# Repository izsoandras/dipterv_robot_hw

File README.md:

# dipterv_robot_hw
The electrical circuit design of my diploma project.

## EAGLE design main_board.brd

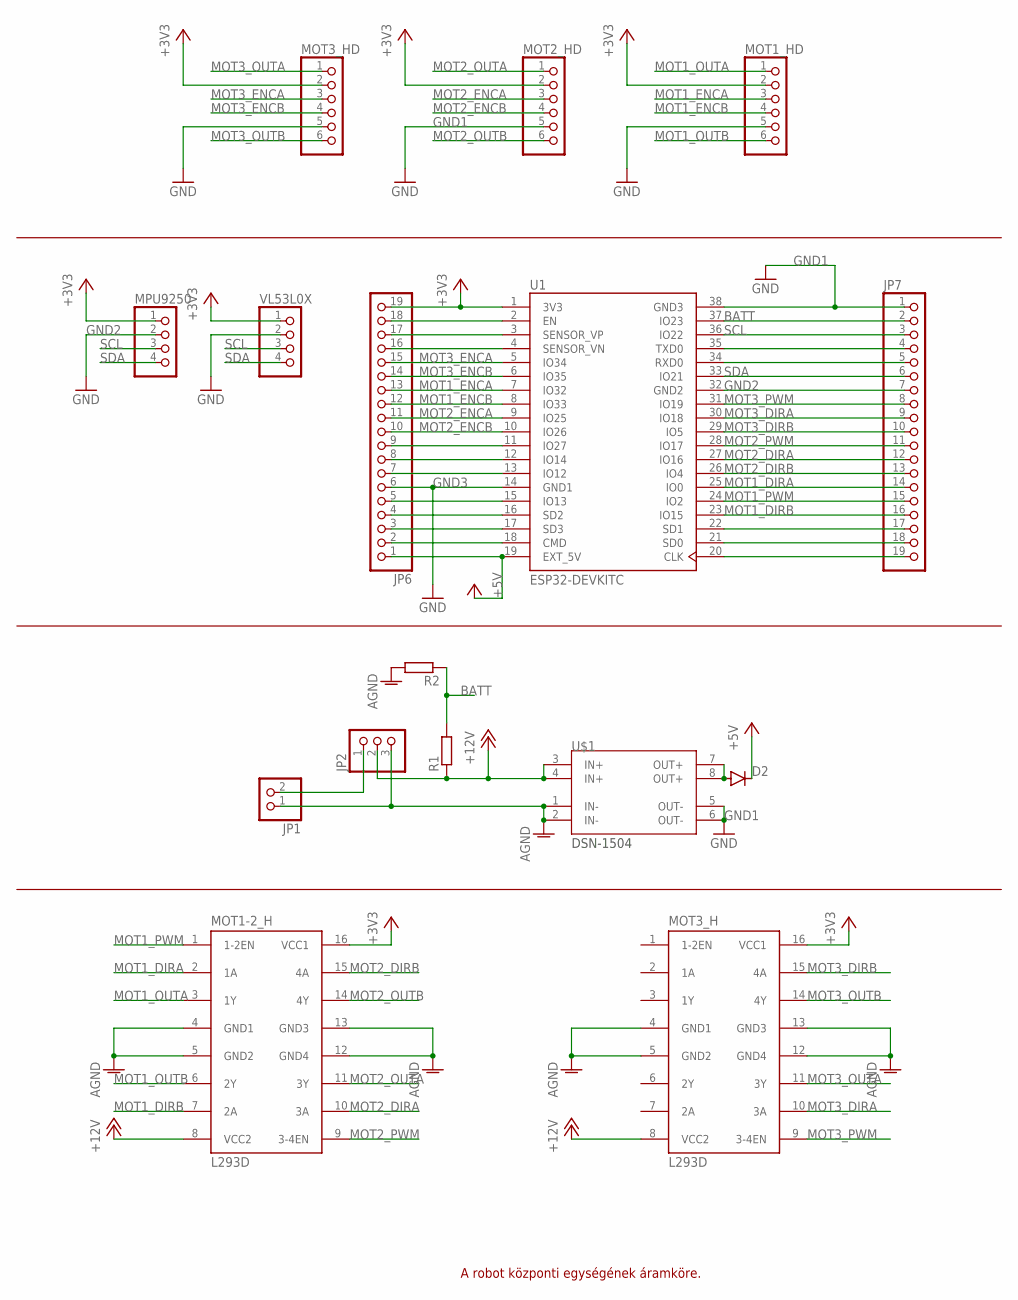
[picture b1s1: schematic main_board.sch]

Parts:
D2: DIODE-DO27-15; DO27-15
JP1: PINHD-1X2; 1X02
JP2: PINHD-1X3; 1X03
JP6, JP7: PINHD-1X19; 1X19
MOT1-2_H, MOT3_H: L293D; DIL16
MOT1_HD, MOT2_HD, MOT3_HD: PINHD-1X6; 1X06
MPU9250: PINHD-1X4; 1X04
R1, R2: R-EU_R0805; R0805
U1: ESP32-DEVKITC; MODULE_ESP32-DEVKITC
U$1: DSN-1504
VL53L0X: PINHD-1X4; 1X04

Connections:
+3V3: JP6.19, MOT1-2_H.16 (VCC1), MOT1_HD.2, MOT2_HD.2, MOT3_H.16 (VCC1), MOT3_HD.2, MPU9250.1, U1.1 (3V3), VL53L0X.1
+5V: D2.C, JP6.1, U1.19 (EXT_5V)
+12V: JP2.2, MOT1-2_H.8 (VCC2), MOT3_H.8 (VCC2), R1.1, U$1.3 (IN+), U$1.4 (IN+)
AGND: JP1.1, JP2.3, MOT1-2_H.4 (GND1), MOT1-2_H.5 (GND2), MOT1-2_H.12 (GND4), MOT1-2_H.13 (GND3), MOT3_H.4 (GND1), MOT3_H.5 (GND2), MOT3_H.12 (GND4), MOT3_H.13 (GND3), R2.2, U$1.1 (IN-), U$1.2 (IN-)
BATT: JP7.2, R1.2, R2.1, U1.37 (IO23)
GND1: JP7.1, MOT2_HD.5, U1.38 (GND3), U$1.5 (OUT-), U$1.6 (OUT-)
GND2: JP7.7, MPU9250.2, U1.32 (GND2)
GND3: JP6.6, MOT1_HD.5, MOT3_HD.5, U1.14 (GND1), VL53L0X.2
MOT1_DIRA: JP7.14, MOT1-2_H.2 (1A), U1.25 (IO0)
MOT1_DIRB: JP7.16, MOT1-2_H.7 (2A), U1.23 (IO15)
MOT1_ENCA: JP6.13, MOT1_HD.3, U1.7 (IO32)
MOT1_ENCB: JP6.12, MOT1_HD.4, U1.8 (IO33)
MOT1_OUTA: MOT1-2_H.3 (1Y), MOT1_HD.1
MOT1_OUTB: MOT1-2_H.6 (2Y), MOT1_HD.6
MOT1_PWM: JP7.15, MOT1-2_H.1 (1-2EN), U1.24 (IO2)
MOT2_DIRA: JP7.12, MOT1-2_H.10 (3A), U1.27 (IO16)
MOT2_DIRB: JP7.13, MOT1-2_H.15 (4A), U1.26 (IO4)
MOT2_ENCA: JP6.11, MOT2_HD.3, U1.9 (IO25)
MOT2_ENCB: JP6.10, MOT2_HD.4, U1.10 (IO26)
MOT2_OUTA: MOT1-2_H.11 (3Y), MOT2_HD.1
MOT2_OUTB: MOT1-2_H.14 (4Y), MOT2_HD.6
MOT2_PWM: JP7.11, MOT1-2_H.9 (3-4EN), U1.28 (IO17)
MOT3_DIRA: JP7.9, MOT3_H.10 (3A), U1.30 (IO18)
MOT3_DIRB: JP7.10, MOT3_H.15 (4A), U1.29 (IO5)
MOT3_ENCA: JP6.15, MOT3_HD.3, U1.5 (IO34)
MOT3_ENCB: JP6.14, MOT3_HD.4, U1.6 (IO35)
MOT3_OUTA: MOT3_H.11 (3Y), MOT3_HD.1
MOT3_OUTB: MOT3_H.14 (4Y), MOT3_HD.6
MOT3_PWM: JP7.8, MOT3_H.9 (3-4EN), U1.31 (IO19)
unnamed: JP6.2, U1.18 (CMD)
unnamed: JP6.3, U1.17 (SD3)
unnamed: JP6.4, U1.16 (SD2)
unnamed: JP1.2, JP2.1
unnamed: D2.A, U$1.7 (OUT+), U$1.8 (OUT+)
unnamed: JP6.8, U1.12 (IO14)
unnamed: JP6.5, U1.15 (IO13)
unnamed: JP6.7, U1.13 (IO12)
unnamed: JP6.9, U1.11 (IO27)
unnamed: JP6.16, U1.4 (SENSOR_VN)
unnamed: JP6.17, U1.3 (SENSOR_VP)
unnamed: JP6.18, U1.2 (EN)
unnamed: JP7.4, U1.35 (TXD0)
unnamed: JP7.5, U1.34 (RXD0)
unnamed: JP7.17, U1.22 (SD1)
unnamed: JP7.18, U1.21 (SD0)
unnamed: JP7.19, U1.20 (CLK)
SCL: JP7.3, MPU9250.3, U1.36 (IO22), VL53L0X.3
SDA: JP7.6, MPU9250.4, U1.33 (IO21), VL53L0X.4

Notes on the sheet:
A robot központi egységének áramköre.

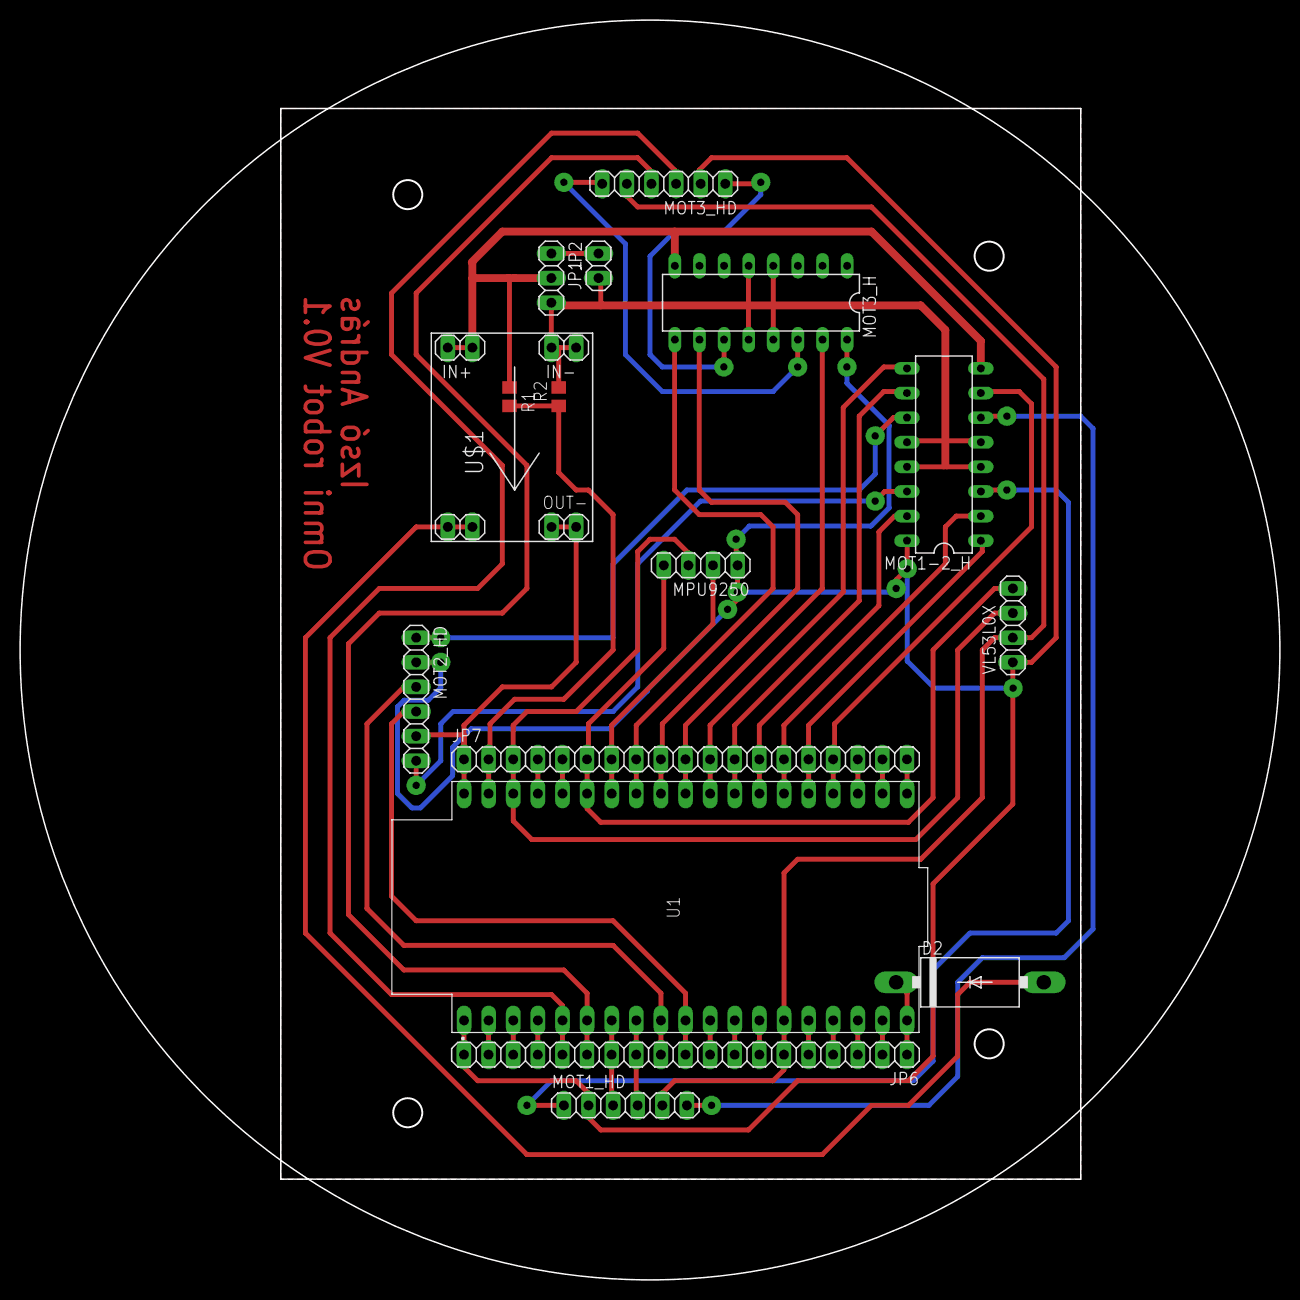
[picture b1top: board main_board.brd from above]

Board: 2 copper layers, 130.0 x 130.0 mm, 16 parts (0 on the bottom side), 48 nets.
